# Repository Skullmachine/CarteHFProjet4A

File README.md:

CarteHFProjet3A
===============

Création d'une carte electronique 3A Polytech'tours

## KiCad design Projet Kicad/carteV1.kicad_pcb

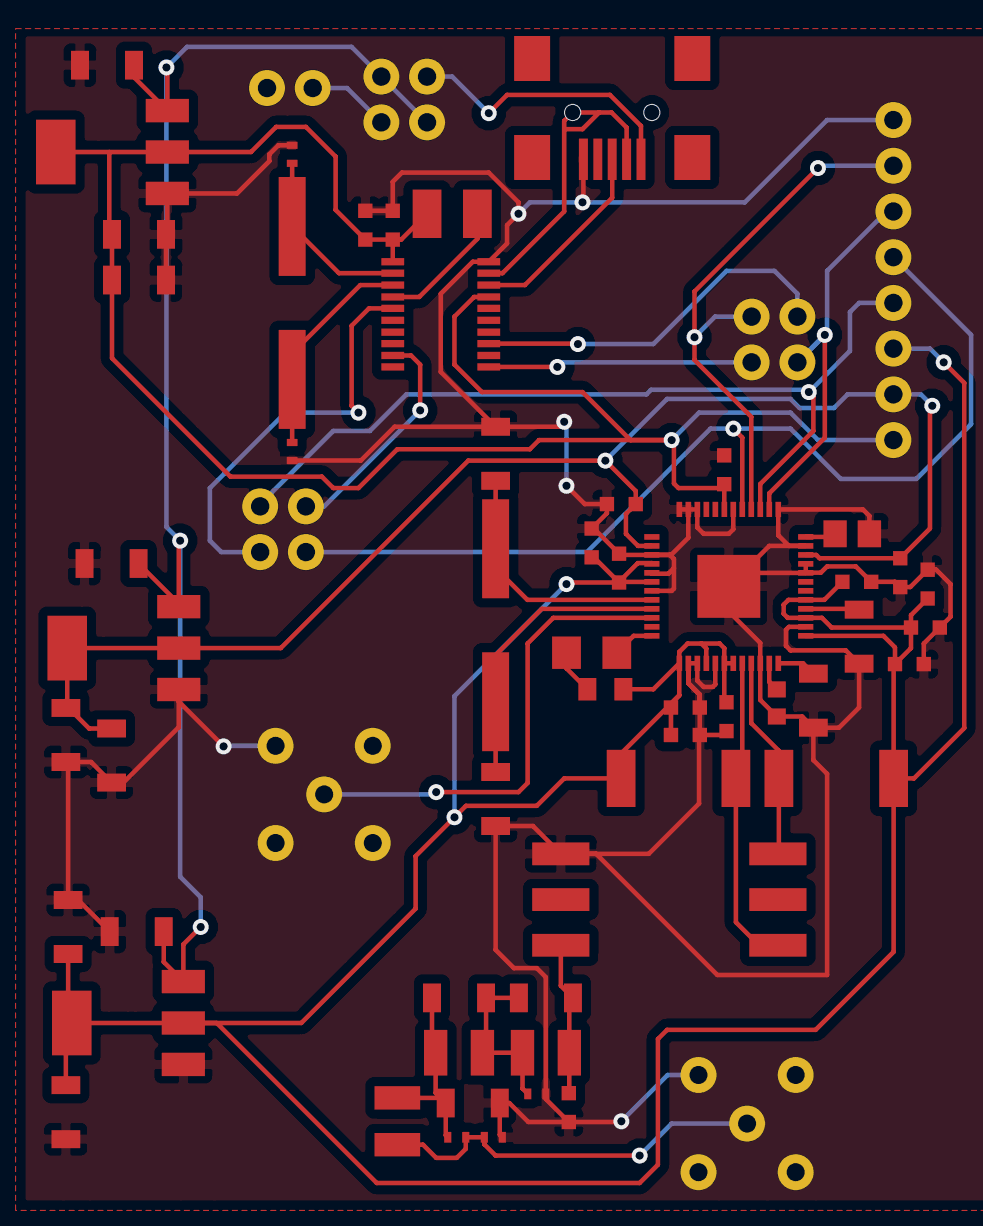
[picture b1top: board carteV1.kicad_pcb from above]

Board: 2 copper layers, 62 parts (0 on the bottom side), 35 nets.

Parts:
C1, C2, C3, C4, C5, C6, C7, C8, C9: 10uF; 1206
C10, C11: 20pF; 0402
C12, C14, C15, C16, C17, C18, C19, C20, C21, C22, C23, C24, C25, C26: 0,1uF; 0603
C13: 2,2pF; 1206
C35, C36: 18pF; 1206
C53, C59: 13pF; 0402
C54: 2.2pF; 1206
C55: 22pF; 0603
C56: 33pF; 0402
C57: 27pF; 1206
C60: 6.8pF; 1206
C61: 0.01μF; 0805
C62: 1μF; 1206
CON1: USB-MINI-B; USB_MINI_B
J7: CRYSTAL OUTDUT2; SMA
J12: FILTER_IOUT_DUT2; SMA
L10: 39nH; 1008CS
L11: 68nH; 1008CS
L12: 56nH; 1008CS
P1, P2, P4: CONN_2X2; BARRETTE_2x2V
P3: CONN_2; BARRETTE_2V
P5: CONN_8; BARRETTE_8V
R1: 3900; r_0805
R9, R21: 25; r_2512
R15: 3.92k; r_0603
R16: 243; r_1206
R1001: 390; r_1210
T8: T1-1T; KK81
U1: AD9954; TQFP48
U2, U3: LM1117MP-1.8; SOT-223
U4: LM1117MP-3.3; SOT-223
U5: MCP2210-SO; SSOP20
X1: 25mhz; HC49/US
X2: 12mhz; HC49/US

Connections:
5V: C1.1, C4.1, C7.1, P2.1, P2.3, U2.3, U3.3, U4.3
/OSC: C11.1, U5.3, X2.1
AVDD: C8.1, C9.1, C17.1, C18.1, C19.1, C20.1, C21.1, C22.1, C23.1, C24.1, C25.1, C61.1, P5.3, R9.2, R21.2, U1.4, U1.6, U1.13, U1.16, U1.18, U1.19, U1.25, U1.27, U1.29, U3.2, U3.4
CHIPSELECT: P4.3, P5.4, U1.39
D+: CON1.2, U5.19
D-: CON1.3, U5.18
DVDD: C5.1, C6.1, C14.1, C15.1, P5.2, U1.2, U1.34, U2.2, U2.4
DVDD_I/O: C2.1, C3.1, C12.2, C16.1, C26.1, P5.1, R1001.1, U1.43, U4.2, U4.4, U5.1, U5.17
GND: C1.2, C2.2, C3.2, C4.2, C5.2, C6.2, C7.2, C8.2, C9.2, C10.2, C11.2, C12.1, C13.2, C14.2, C15.2, C16.2, C17.2, C18.2, C19.2, C20.2, C21.2, C22.2, C23.2, C24.2, C25.2, C26.2, C35.1, C36.2, C55.2, C56.2, C57.2, C59.2, C62.2, CON1.5, J7.2, J7.3, J7.4, J7.5, J12.2, J12.3, J12.4, J12.5, P3.1, P5.8, R1.2, R15.2, T8.6, U1.3, U1.5, U1.7, U1.14, U1.15, U1.17, U1.22, U1.26, U1.32, U1.33, U1.35, U1.37, U1.42, U1.46, U1.47, U1.48, U1.49, U2.1, U3.1, U4.1, U5.20
MISO: P1.3, P5.6, U1.38
MOSI: P4.1, P5.5, U1.41
unnamed: C61.2, R16.1
unnamed: R16.2, U1.12
unnamed: C36.1, U1.8, X1.2
unnamed: C35.2, U1.9, X1.1
unnamed: P1.4, U5.13
unnamed: P4.2, U5.9
unnamed: R1.1, U1.36
unnamed: P1.2, U5.11
unnamed: C53.1, C59.1, J12.1, L10.1
unnamed: C53.2, C57.1, C60.1, L10.2, L12.1
unnamed: C54.1, C56.1, C60.2, L11.1, L12.2
unnamed: C13.1, U1.28
unnamed: CON1.1, P2.4
unnamed: P2.2, P3.2
unnamed: C62.1, U1.24
unnamed: C54.2, C55.1, L11.2, T8.4
unnamed: P4.4, U5.5
unnamed: R15.1, U1.23
unnamed: R21.1, T8.3, U1.20
unnamed: R9.1, T8.1, U1.21
unnamed: R1001.2, U5.4
OSC: C10.1, U5.2, X2.2
SCK: P1.1, P5.7, U1.40
XTAL_AUTO: J7.1, U1.10

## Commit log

2014-05-18 ménage
2014-05-18 Add some documentations
2014-05-18 REPAIR AD9954
    -Mistext
2014-05-18 Add docs
2014-05-18 Ajout GND AVDD
2014-05-18 Mise en forme de la page
2014-05-18 Rajout de la partie XTAL
2014-05-18 Filtre
2014-05-18 Avancement
    -Rajout d’une partie du filtrage..
2014-05-19 Installation du Quartz
    -Détermination des capa
    -Determination du quartz
2014-05-19 Avancement
    - Ajout de la lib MAX.. SPI/USB
    - Ajout d’un connecteur MINI USB
    -Ajout d’un convertisseur CC … plus qu’a le câblé
2014-05-19 Modification : Alimentation & USB
    -Ajout des 2 alimentations + ref
    -Modification du MAX
2014-05-20 USB changement PARTS
    -Utilisation du MCP2210 ( SPI-MASTER)
    -Changement du Quartz
2014-05-20 Alimentation
    -Ajout des deux montages
    -Fin du raccordement du microC
2014-05-20 Ajout des titres
2014-05-21 Réparation des fils
2014-05-21 Reparation fils
2014-05-22 Numérotation des composants
2014-05-22 Ajout des footprints et liaisons
2014-05-22 Add MP2210 documentation and supply MP2210 with 3,3V
2014-05-26 Ajout jumper
2014-05-27 modification ad9954
2014-05-27 modif AD9954
2014-05-27 Modif pcb
2014-06-03 Remove the test point of ref_clk
2014-06-05 Insertion capa pour découplage + new footprint
2014-06-05 Modify the connector to power in 5V
2014-06-13 Ajout du fichier pour la commande, typon terminé avec plan de masse
2014-06-15 Final version without the I/O update pin connected
2014-11-10 Ajout rapport & modification schéma structurel
2014-11-19 Modification du schéma structurel: - Ajout des 3 alimentations à découpage
2014-11-19 AJout datasheet rl-5530 (Transformateur 22uH)
2015-02-01 Ajout liste des composants possédés
2015-02-01 Ajout fichier commande de composants
2015-02-01 Ajout du Gantt prévisionnel
2015-02-01 Ajout schéma structurel alimentation AD9954
    Compatible Multisim v13
2015-02-01 Maj schéma structurel Kicad
2015-02-05 Maj schema structurel
2015-02-05 Maj AD9954
2015-02-18 Finalisation Schema structurel
2015-02-18 Correction netlist Source
2015-02-21 Maj Commande Farnell
2015-02-24 MAJ CartProjetHF4A
2015-02-24 MAJ CarteProjetHF4A
2015-02-24 MAJ
    supression resistance 3.9 k et polarisation C13
2015-02-24 Màj CarteProjetHF4A
2015-02-24 MAJ CarteProjetHF4A
    Nom des pins AD9959
2015-02-24 Màj schéma structurel
2015-02-24 Ajout photos du schéma structurel annoté
2015-02-25 Màj Commandes
2015-02-25 Màj des schémas
2015-02-28 Ajout liste composants pour Altais
2015-03-06 Empreintes des composants r Please enter the commit message for your changes. Lines starting
